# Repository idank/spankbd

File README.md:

# Span keyboard

Span is a low profile split keyboard with 3x5 column staggered keys with 2u, 1.5u, 1u thumb clusters.

The keyboard layout is derived from GergoPlex, a keyboard that was originally available on gboards.ca
(now defunct).

Features:

* 18x17 mm choc spacing.
* Optional 2u choc stabilizer.
* OLED support.
* Hybrid hotswap / direct soldering for switches.

The pcbs aren't reversible at the moment: I prefer the cleaner look of the top
side and generally think it's easier to deal with. A reversible version may be
added in the future.

## Availability

Kits and built keyboards can be purchased on *[holykeebs](https://holykeebs.com)*.

Gerber files are available in the releases page.

## Guide

See this [page](https://docs.holykeebs.com/guides/keyboard/).

## License

This work is licensed under a
[Creative Commons Attribution-ShareAlike 4.0 International License][cc-by-sa].

[cc-by-sa]: http://creativecommons.org/licenses/by-sa/4.0/

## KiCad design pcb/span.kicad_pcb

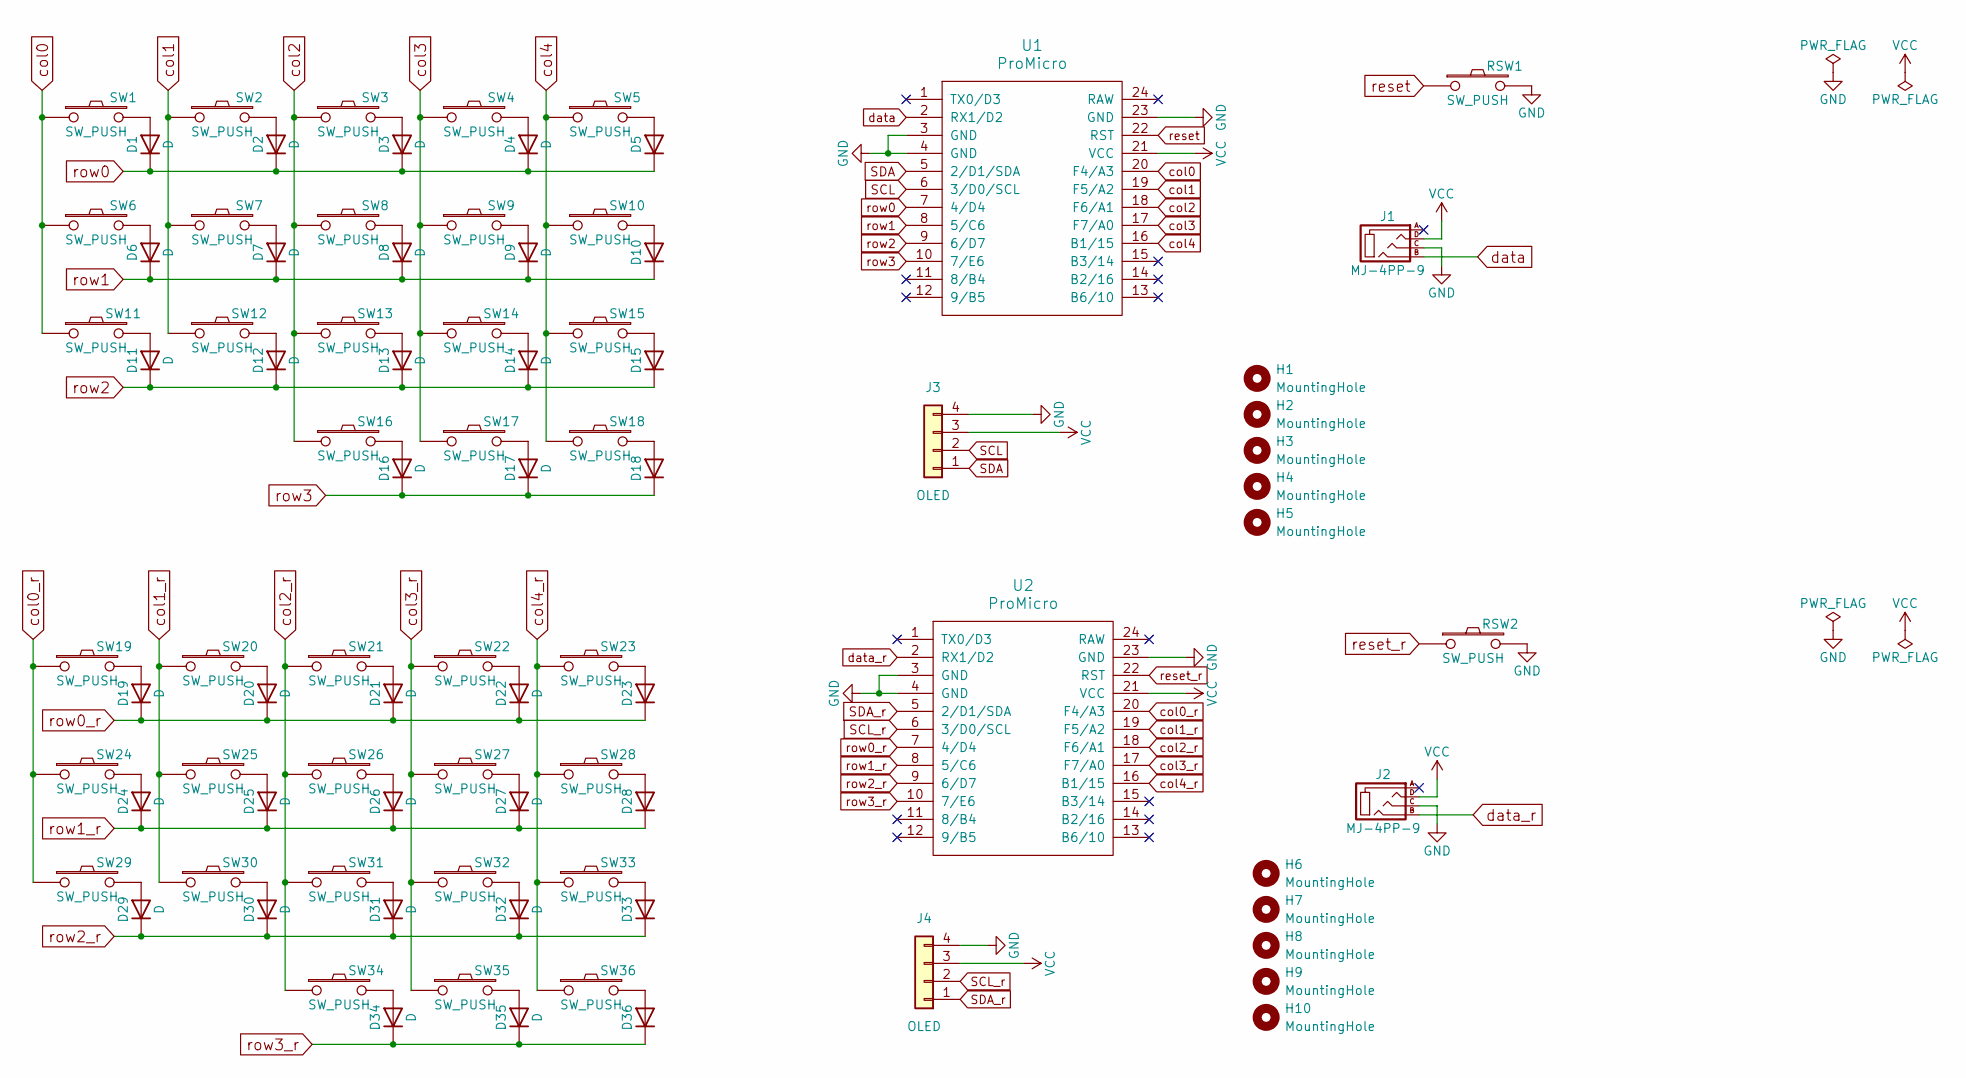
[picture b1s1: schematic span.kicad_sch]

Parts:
D1, D2, D3, D4, D5, D6, D7, D8, D9, D10, D11, D12, D13, D14, D15, D16, D17, D18, D19, D20, D21, D22, D23, D24, D25, D26, D27, D28, D29, D30, D31, D32, D33, D34, D35, D36: D; D3_SMD_v2
H1, H2, H3, H4, H5, H6, H7, H8, H9, H10: MountingHole; M2_SPACER
J1, J2: MJ-4PP-9; MJ-4PP-9_1side
J3, J4: OLED; OLED_1side
RSW1, RSW2: SW_PUSH; RSW_2PIN_SMD
SW1, SW2, SW3, SW4, SW5, SW6, SW7, SW8, SW9, SW10, SW11, SW12, SW13, SW14, SW15, SW16, SW17, SW19, SW20, SW21, SW22, SW23, SW24, SW25, SW26, SW27, SW28, SW29, SW30, SW31, SW32, SW33, SW34, SW35: SW_PUSH; Kailh_socket_PG1350_optional_oval_smaller_hotswap
SW18, SW36: SW_PUSH; Kailh_socket_PG1350_2u_optional_oval
U1, U2: ProMicro; ProMicro_1mm_holes

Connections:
GND: J1.C, J2.C, J3.4, J4.4, RSW1.2, RSW2.2, U1.3 (GND), U1.4 (GND), U1.23 (GND), U2.3 (GND), U2.4 (GND), U2.23 (GND)
unnamed: D1.2 (A), SW1.2
unnamed: D2.2 (A), SW2.2
unnamed: D3.2 (A), SW3.2
unnamed: D4.2 (A), SW4.2
unnamed: D5.2 (A), SW5.2
unnamed: D6.2 (A), SW6.2
unnamed: D7.2 (A), SW7.2
unnamed: D8.2 (A), SW8.2
unnamed: D9.2 (A), SW9.2
unnamed: D10.2 (A), SW10.2
unnamed: D11.2 (A), SW11.2
unnamed: D12.2 (A), SW12.2
unnamed: D13.2 (A), SW13.2
unnamed: D14.2 (A), SW14.2
unnamed: D15.2 (A), SW15.2
unnamed: D16.2 (A), SW16.2
unnamed: D17.2 (A), SW17.2
unnamed: D18.2 (A), SW18.2
unnamed: D19.2 (A), SW19.2
unnamed: D20.2 (A), SW20.2
unnamed: D21.2 (A), SW21.2
unnamed: D22.2 (A), SW22.2
unnamed: D23.2 (A), SW23.2
unnamed: D24.2 (A), SW24.2
unnamed: D25.2 (A), SW25.2
unnamed: D26.2 (A), SW26.2
unnamed: D27.2 (A), SW27.2
unnamed: D28.2 (A), SW28.2
unnamed: D29.2 (A), SW29.2
unnamed: D30.2 (A), SW30.2
unnamed: D31.2 (A), SW31.2
unnamed: D32.2 (A), SW32.2
unnamed: D33.2 (A), SW33.2
unnamed: D34.2 (A), SW34.2
unnamed: D35.2 (A), SW35.2
unnamed: D36.2 (A), SW36.2
SCL: J3.2, U1.6 (3/D0/SCL)
SCL_r: J4.2, U2.6 (3/D0/SCL)
SDA: J3.1, U1.5 (2/D1/SDA)
SDA_r: J4.1, U2.5 (2/D1/SDA)
VCC: J1.D, J2.D, J3.3, J4.3, U1.21 (VCC), U2.21 (VCC)
col0: SW1.1, SW6.1, SW11.1, U1.20 (F4/A3)
col0_r: SW19.1, SW24.1, SW29.1, U2.20 (F4/A3)
col1: SW2.1, SW7.1, SW12.1, U1.19 (F5/A2)
col1_r: SW20.1, SW25.1, SW30.1, U2.19 (F5/A2)
col2: SW3.1, SW8.1, SW13.1, SW16.1, U1.18 (F6/A1)
col2_r: SW21.1, SW26.1, SW31.1, SW34.1, U2.18 (F6/A1)
col3: SW4.1, SW9.1, SW14.1, SW17.1, U1.17 (F7/A0)
col3_r: SW22.1, SW27.1, SW32.1, SW35.1, U2.17 (F7/A0)
col4: SW5.1, SW10.1, SW15.1, SW18.1, U1.16 (B1/15)
col4_r: SW23.1, SW28.1, SW33.1, SW36.1, U2.16 (B1/15)
data: J1.B, U1.2 (RX1/D2)
data_r: J2.B, U2.2 (RX1/D2)
reset: RSW1.1, U1.22 (RST)
reset_r: RSW2.1, U2.22 (RST)
row0: D1.1 (K), D2.1 (K), D3.1 (K), D4.1 (K), D5.1 (K), U1.7 (4/D4)
row0_r: D19.1 (K), D20.1 (K), D21.1 (K), D22.1 (K), D23.1 (K), U2.7 (4/D4)
row1: D6.1 (K), D7.1 (K), D8.1 (K), D9.1 (K), D10.1 (K), U1.8 (5/C6)
row1_r: D24.1 (K), D25.1 (K), D26.1 (K), D27.1 (K), D28.1 (K), U2.8 (5/C6)
row2: D11.1 (K), D12.1 (K), D13.1 (K), D14.1 (K), D15.1 (K), U1.9 (6/D7)
row2_r: D29.1 (K), D30.1 (K), D31.1 (K), D32.1 (K), D33.1 (K), U2.9 (6/D7)
row3: D16.1 (K), D17.1 (K), D18.1 (K), U1.10 (7/E6)
row3_r: D34.1 (K), D35.1 (K), D36.1 (K), U2.10 (7/E6)

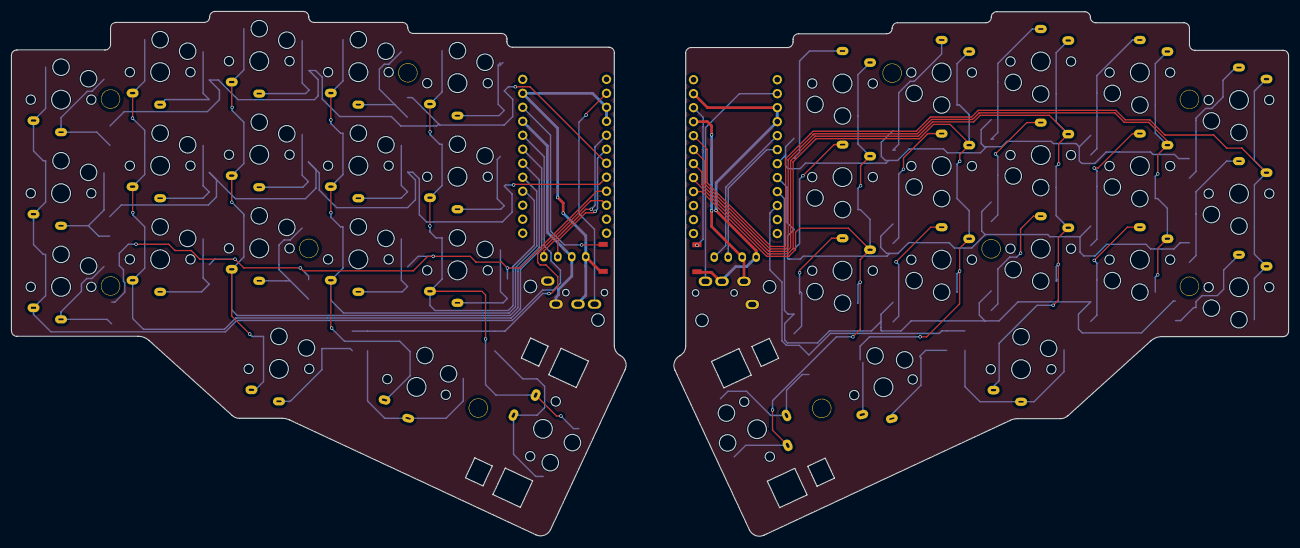
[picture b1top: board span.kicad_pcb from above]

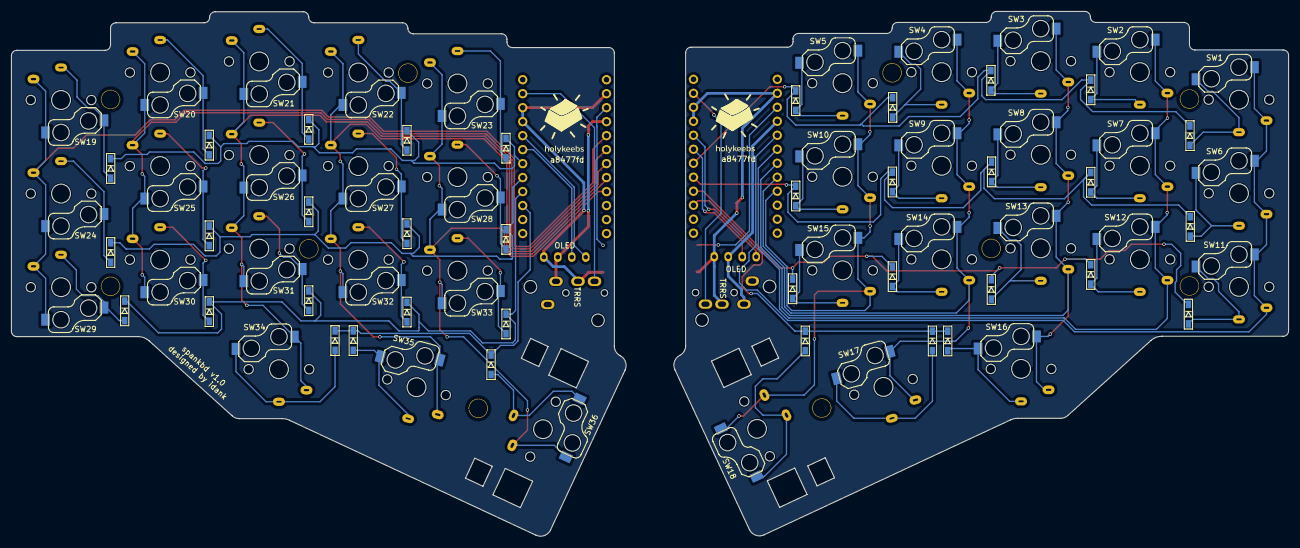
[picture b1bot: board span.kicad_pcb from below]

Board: 2 copper layers, 232.0 x 95.3 mm, 90 parts (41 on the bottom side), 64 nets.

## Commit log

2023-09-13 pcb: bump version
2023-09-14 readme: add note regarding gerber files
2023-09-14 pcb: ungroup left / right mounting holes
2023-09-19 misc: add acrylic plate, oled dxf files
2023-11-22 readme: add link to guide
2024-01-23 pcb: enlarge m2 holes to 3.2 mm to allow a bit more slop
2024-01-23 pcb: add holykeebs logo, fix attribution
2024-02-13 pcb: use slightly bigger holes for the controller pins and mounting holes
2024-09-23 pcb: add filled zones
2024-11-08 add LICENSE
